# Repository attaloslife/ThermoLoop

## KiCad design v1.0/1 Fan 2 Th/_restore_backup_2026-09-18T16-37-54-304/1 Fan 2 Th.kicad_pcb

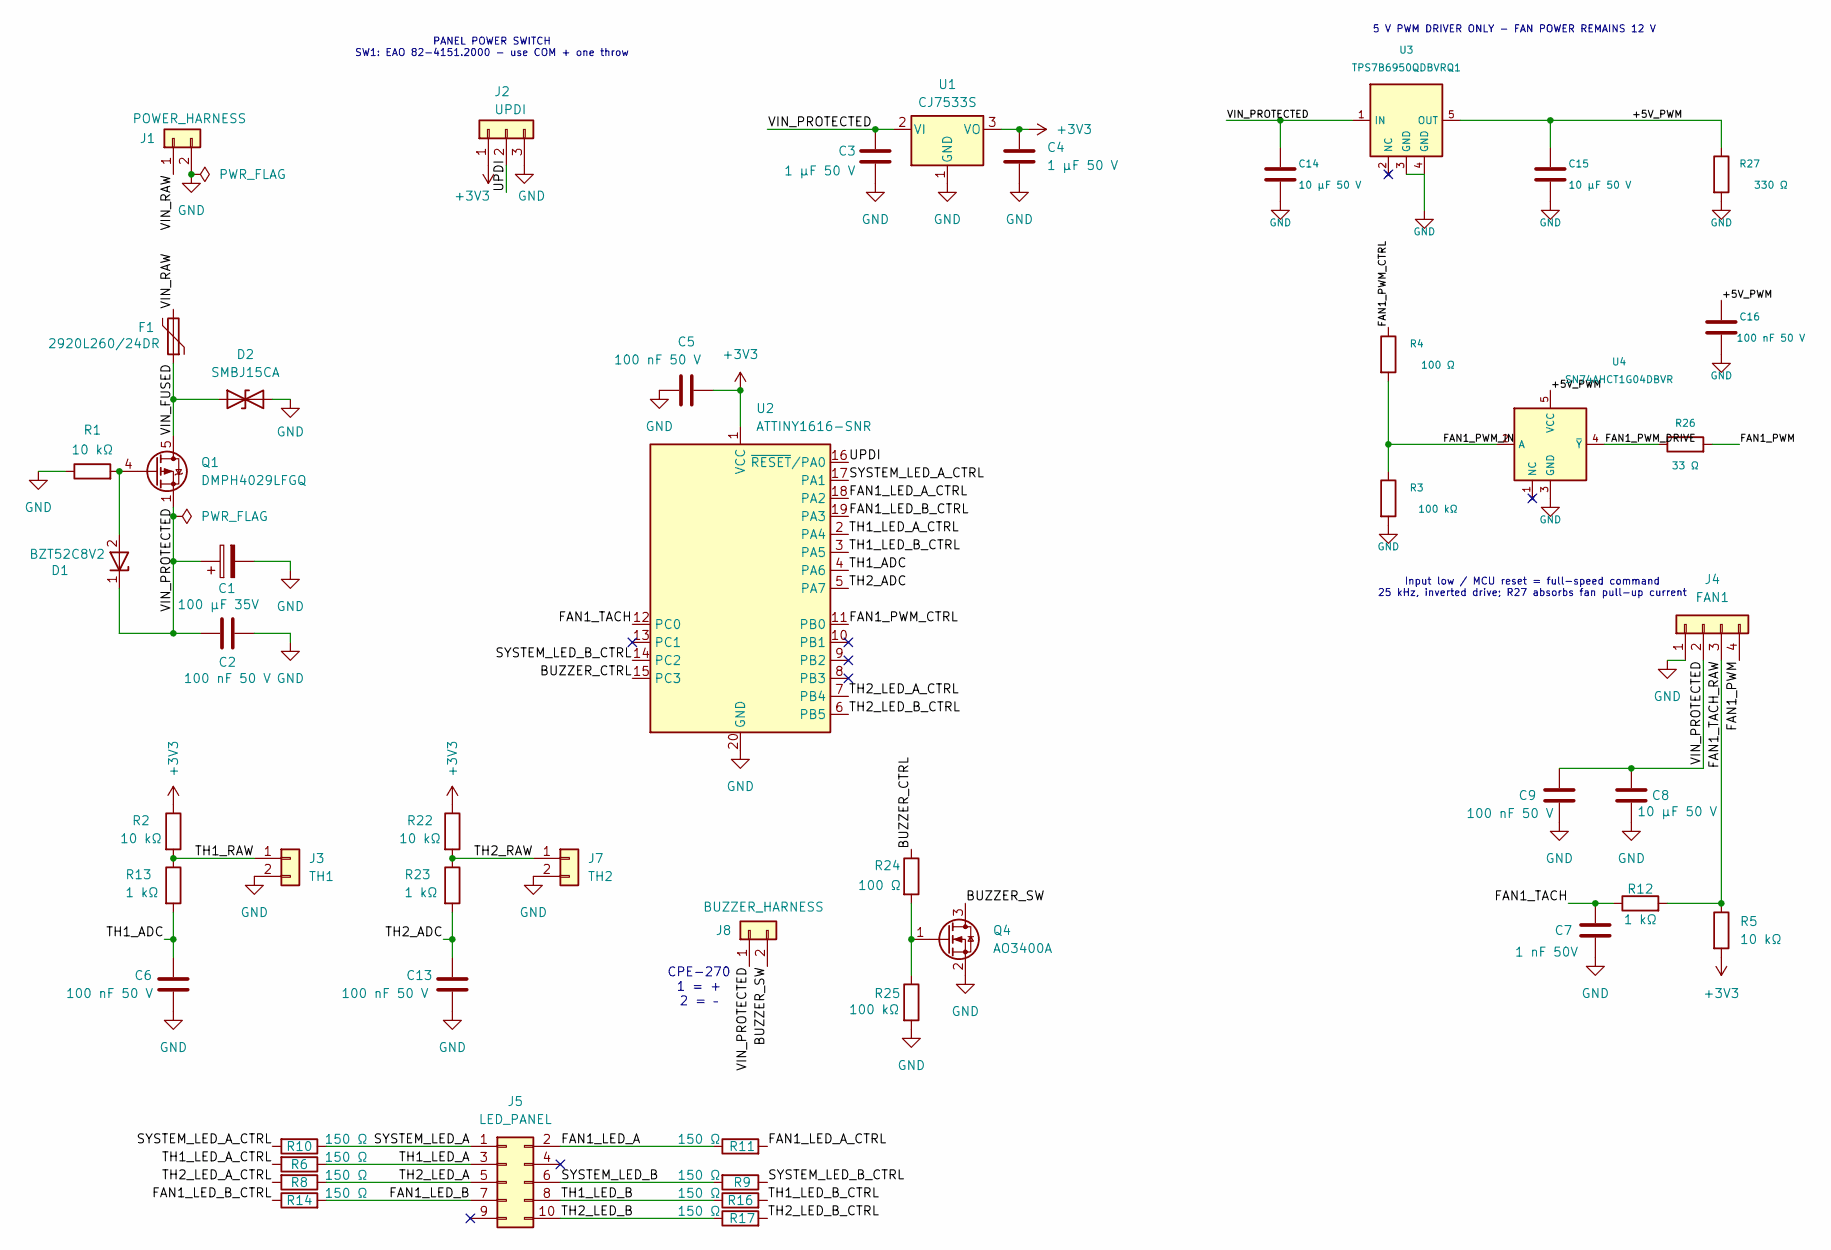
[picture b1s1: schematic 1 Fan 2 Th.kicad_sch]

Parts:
C1: 100 µF 35V; CP_Elec_6.3x7.7; MPN VZH101M1VTR-0607; JLCPCB C176683
C2, C5, C6, C9, C13, C16: 100 nF 50 V; C_0805_2012Metric; Tolerance ±10%; MPN CC0805KRX7R9BB104; JLCPCB C49678
C3, C4: 1 µF 50 V; C_0805_2012Metric; Tolerance ±10%; MPN CL21B105KBFNNNE; JLCPCB C28323
C7: 1 nF 50V; C_0805_2012Metric; Tolerance ±10%; MPN CL21B102KBCNNNC; JLCPCB C46653
C8, C14, C15: 10 µF 50 V; C_1210_3225Metric; MPN CL32B106KBJNNNE; JLCPCB C138687
D1: BZT52C8V2; D_SOD-123; MPN BZT52C8V2; JLCPCB C173432
D2: SMBJ15CA; D_SMB; MPN SMBJ15CA; JLCPCB C78809
F1: 2920L260/24DR; Fuse_2920_7451Metric; MPN 2920L260/24DR; JLCPCB C315904
J1: POWER_HARNESS; Molex_Micro-Fit_3.0_43045-0218_2x01-1MP_P3.00mm_Vertical; MPN 43045-0218; JLCPCB C476811
J2: UPDI; PinHeader_1x03_P2.54mm_Vertical; MPN 2.54-1*3PPin; JLCPCB C49257
J3: TH1; Molex_Micro-Fit_3.0_43045-0218_2x01-1MP_P3.00mm_Vertical; MPN 43045-0218; JLCPCB C476811
J4: FAN1; Molex_Micro-Fit_3.0_43045-0418_2x02-1MP_P3.00mm_Vertical; MPN 43045-0418; JLCPCB C293535
J5: LED_PANEL; Molex_Micro-Fit_3.0_43045-1018_2x05-1MP_P3.00mm_Vertical; MPN 43045-1018; JLCPCB C476814
J7: TH2; Molex_Micro-Fit_3.0_43045-0218_2x01-1MP_P3.00mm_Vertical; MPN 43045-0218; JLCPCB C476811
J8: BUZZER_HARNESS; Molex_Micro-Fit_3.0_43045-0218_2x01-1MP_P3.00mm_Vertical; MPN 43045-0218; JLCPCB C476811
Q1: DMPH4029LFGQ; Diodes_PowerDI3333-8; MPN DMPH4029LFGQ-7; JLCPCB C3279395
Q4: AO3400A; SOT-23; MPN AO3400A; JLCPCB C20917
R1, R2, R5, R22: 10 kΩ; R_0603_1608Metric; Tolerance ±1%; MPN 0603WAF1002T5E; JLCPCB C25804
R3, R25: 100 kΩ; R_0603_1608Metric; Tolerance ±1%; MPN 0603WAF1003T5E; JLCPCB C25803
R4, R24: 100 Ω; R_0603_1608Metric; Tolerance ±1%; MPN 0603WAF1000T5E; JLCPCB C22775
R6, R8, R9, R10, R11, R14, R16, R17: 150 Ω; R_0603_1608Metric; Tolerance ±1%; MPN 0603WAF1500T5E; JLCPCB C22808
R12, R13, R23: 1 kΩ; R_0603_1608Metric; Tolerance ±1%; MPN 0603WAF1001T5E; JLCPCB C21190
R26: 33 Ω; R_0603_1608Metric; Tolerance ±1%; MPN 0603WAF330JT5E; JLCPCB C23140
R27: 330 Ω; R_0805_2012Metric; Tolerance ±1%; MPN 0805W8F3300T5E; JLCPCB C17630
U1: CJ7533S; SOT-89-3; MPN CJ7533S; JLCPCB C2829417
U2: ATTINY1616-SNR; SOIC-20W_7.5x12.8mm_P1.27mm; MPN ATTINY1616-SNR; JLCPCB C609652
U3: TPS7B6950QDBVRQ1; SOT-23-5; MPN TPS7B6950QDBVRQ1; JLCPCB C132202
U4: SN74AHCT1G04DBVR; SOT-23-5; MPN SN74AHCT1G04DBVR; JLCPCB C30326

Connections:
+3V3: C4.1, C5.1, J2.1, R2.1, R5.2, R22.1, U1.3 (VO), U2.1 (VCC)
/+5V_PWM: C15.1, C16.1, R27.1, U3.5 (OUT), U4.5 (VCC)
/BUZZER_CTRL: R24.1, U2.15 (PC3)
/BUZZER_SW: J8.2, Q4.3 (D)
/FAN1_LED_A: J5.2, R11.1
/FAN1_LED_A_CTRL: R11.2, U2.18 (PA2)
/FAN1_LED_B: J5.7, R14.2
/FAN1_LED_B_CTRL: R14.1, U2.19 (PA3)
/FAN1_PWM: J4.4, R26.2
/FAN1_PWM_CTRL: R4.1, U2.11 (PB0)
/FAN1_PWM_DRIVE: R26.1, U4.4 (~Y)
/FAN1_PWM_IN: R3.1, R4.2, U4.2 (A)
/FAN1_TACH: C7.1, R12.1, U2.12 (PC0)
/FAN1_TACH_RAW: J4.3, R5.1, R12.2
/SYSTEM_LED_A: J5.1, R10.1
/SYSTEM_LED_A_CTRL: R10.2, U2.17 (PA1)
/SYSTEM_LED_B: J5.6, R9.2
/SYSTEM_LED_B_CTRL: R9.1, U2.14 (PC2)
/TH1_ADC: C6.1, R13.2, U2.4 (PA6)
/TH1_LED_A: J5.3, R6.1
/TH1_LED_A_CTRL: R6.2, U2.2 (PA4)
/TH1_LED_B: J5.8, R16.1
/TH1_LED_B_CTRL: R16.2, U2.3 (PA5)
/TH1_RAW: J3.1, R2.2, R13.1
/TH2_ADC: C13.1, R23.2, U2.5 (PA7)
/TH2_LED_A: J5.5, R8.1
/TH2_LED_A_CTRL: R8.2, U2.7 (PB4)
/TH2_LED_B: J5.10, R17.1
/TH2_LED_B_CTRL: R17.2, U2.6 (PB5)
/TH2_RAW: J7.1, R22.2, R23.1
/UPDI: J2.2, U2.16 (~RESET/PA0)
/VIN_FUSED: D2.1 (A1), F1.1, Q1.5 (D)
/VIN_PROTECTED: C1.1, C2.1, C3.1, C8.1, C9.1, C14.1, D1.1 (K), J4.2, J8.1, Q1.1 (S), Q1.2 (S), Q1.3 (S), U1.2 (VI), U3.1 (IN)
/VIN_RAW: F1.2, J1.1
GND: C1.2, C2.2, C3.2, C4.2, C5.2, C6.2, C7.2, C8.2, C9.2, C13.2, C14.2, C15.2, C16.2, D2.2 (A2), J1.2, J2.3, J3.2, J4.1, J7.2, Q4.2 (S), R1.1, R3.2, R25.2, R27.2, U1.1 (GND), U2.20 (GND), U3.3 (GND), U3.4 (GND), U4.3 (GND)
unnamed: D1.2 (A), Q1.4 (G), R1.2
unnamed: Q4.1 (G), R24.2, R25.1

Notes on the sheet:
PANEL POWER SWITCH SW1: EAO 82-4151.2000 - use COM + one throw
CPE-270 1 = + 2 = –
5 V PWM DRIVER ONLY - FAN POWER REMAINS 12 V
Input low / MCU reset = full-speed command 25 kHz, inverted drive; R27 absorbs fan pull-up current

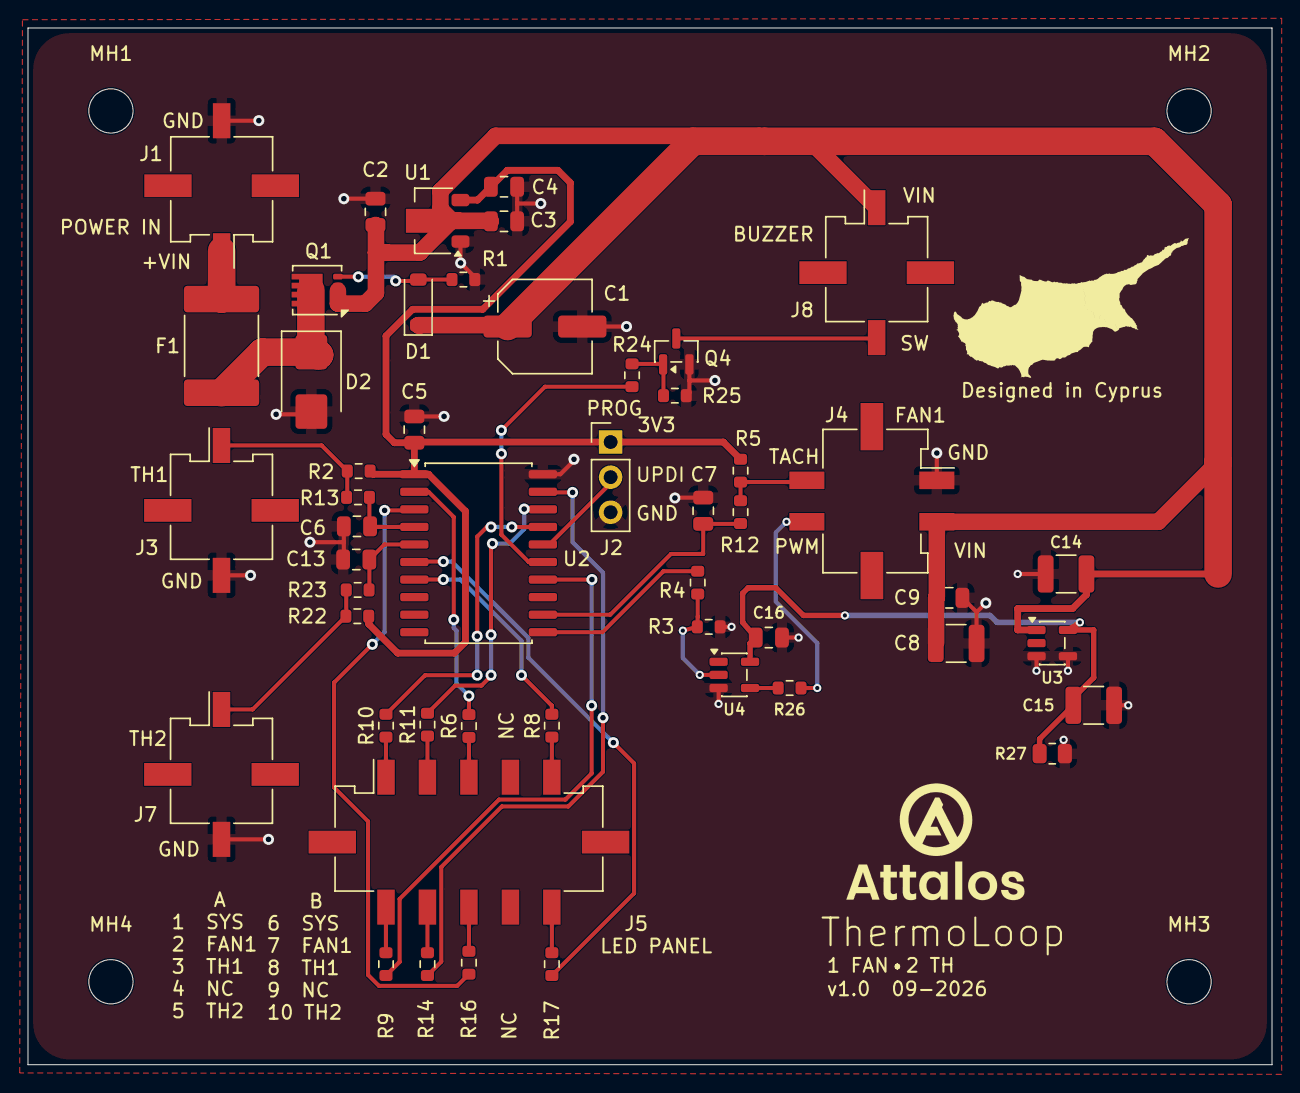
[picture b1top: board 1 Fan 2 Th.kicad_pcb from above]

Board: 2 copper layers, 90.0 x 75.0 mm, 54 parts (0 on the bottom side), 37 nets.

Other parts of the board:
MH1, MH2, MH3, MH4: MountingHole_3.2mm_M3

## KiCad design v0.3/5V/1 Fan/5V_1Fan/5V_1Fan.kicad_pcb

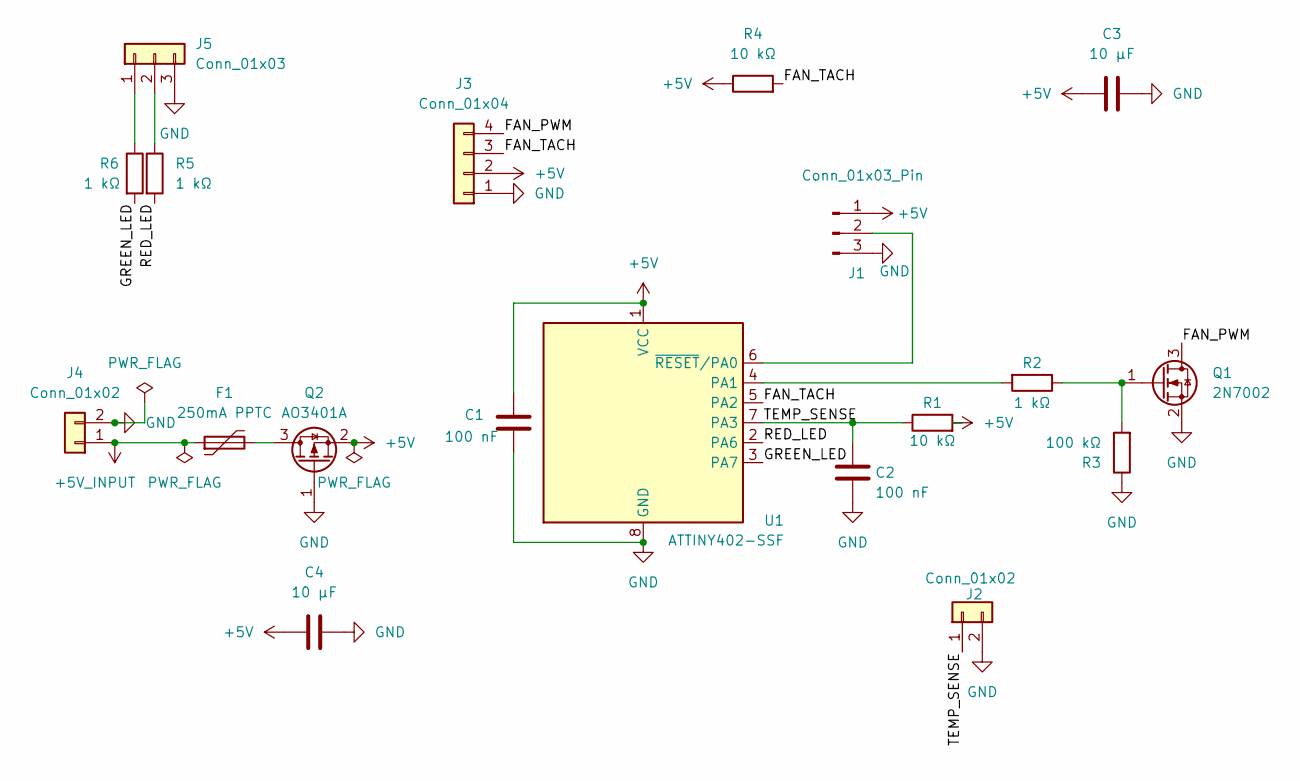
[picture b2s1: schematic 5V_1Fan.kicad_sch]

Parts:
C1, C2: 100 nF; C_0805_2012Metric_Pad1.18x1.45mm_HandSolder; MPN GRM21BR71H104KA01L; JLCPCB Part C77082
C3, C4: 10 µF; C_1206_3216Metric_Pad1.33x1.80mm_HandSolder; MPN TCC1206X7R106K160HT; JLCPCB Part C380363
F1: 250mA PPTC; Fuse_1206_3216Metric_Pad1.42x1.75mm_HandSolder; MPN 1206L025/24YR; JLCPCB Part C3762322
J1: Conn_01x03_Pin; PinHeader_1x03_P2.54mm_Vertical; MPN 2.54-1*3; JLCPCB Part C5116482
J2: Conn_01x02; JST_PH_B2B-PH-K_1x02_P2.00mm_Vertical; MPN B2B-PH-K-S; JLCPCB Part C20504437
J3: Conn_01x04; FanPinHeader_1x04_P2.54mm_Vertical; MPN 470531000; JLCPCB Part C240840
J4: Conn_01x02; JST_XH_B2B-XH-A_1x02_P2.50mm_Vertical; MPN B2B-XH-A(LF)(SN); JLCPCB Part C158012
J5: Conn_01x03; JST_PH_B3B-PH-K_1x03_P2.00mm_Vertical; MPN B3B-PH-K-S(LF)(SN); JLCPCB Part C131339
Q1: 2N7002; SOT-23; MPN 2N7002; JLCPCB Part C389059
Q2: AO3401A; SOT-23; MPN AO3401A; JLCPCB Part C15127
R1, R4: 10 kΩ; R_0805_2012Metric_Pad1.20x1.40mm_HandSolder; MPN RC0805FR-0710KL; JLCPCB Part C84376
R2, R5, R6: 1 kΩ; R_0805_2012Metric_Pad1.20x1.40mm_HandSolder; MPN RC0805FR-071KL; JLCPCB Part C95781
R3: 100 kΩ; R_0805_2012Metric_Pad1.20x1.40mm_HandSolder; MPN RC0805FR-07100KL; JLCPCB Part C96346
U1: ATTINY402-SSF; SOIC-8_3.9x4.9mm_P1.27mm; MPN ATTINY402-SSF; JLCPCB Part C1338236

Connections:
+5V: C1.1, C3.2, C4.1, J1.1, J3.2, Q2.2 (S), R1.2, R4.1, U1.1 (VCC)
+5V_INPUT: F1.1, J4.1
/FAN_PWM: J3.4, Q1.3 (D)
/FAN_TACH: J3.3, R4.2, U1.5 (PA2)
/GREEN_LED: R6.2, U1.3 (PA7)
/RED_LED: R5.2, U1.2 (PA6)
/TEMP_SENSE: C2.1, J2.1, R1.1, U1.7 (PA3)
GND: C1.2, C2.2, C3.1, C4.2, J1.3, J2.2, J3.1, J4.2, J5.3, Q1.2 (S), Q2.1 (G), R3.1, U1.8 (GND)
unnamed: J1.2, U1.6 (~RESET/PA0)
unnamed: J5.1, R6.1
unnamed: J5.2, R5.1
unnamed: Q1.1 (G), R2.1, R3.2
unnamed: F1.2, Q2.3 (D)
unnamed: R2.2, U1.4 (PA1)

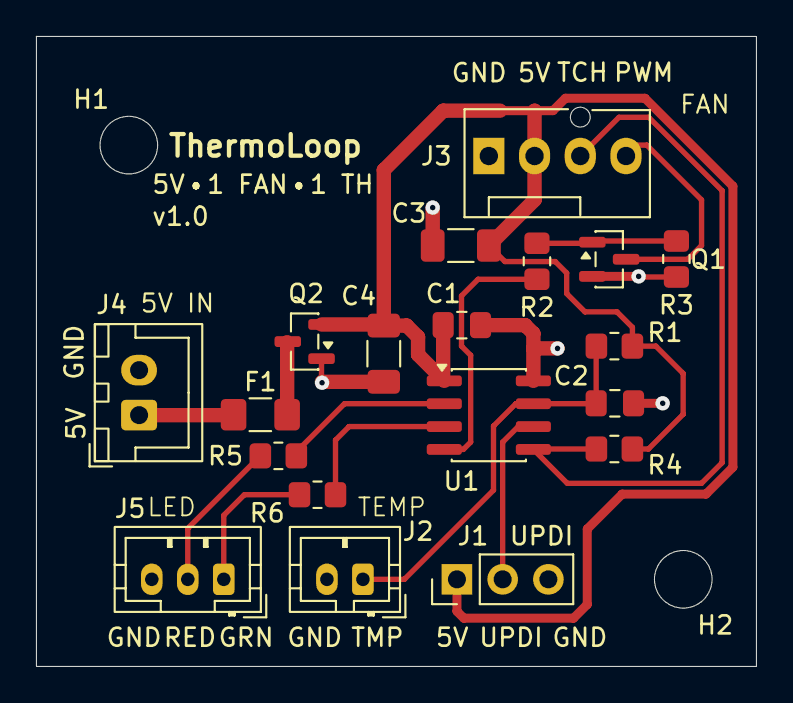
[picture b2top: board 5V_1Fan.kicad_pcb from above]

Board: 2 copper layers, 40.0 x 35.0 mm, 21 parts (0 on the bottom side), 14 nets.

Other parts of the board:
H1, H2: MountingHole_3.2mm_M3_DIN965

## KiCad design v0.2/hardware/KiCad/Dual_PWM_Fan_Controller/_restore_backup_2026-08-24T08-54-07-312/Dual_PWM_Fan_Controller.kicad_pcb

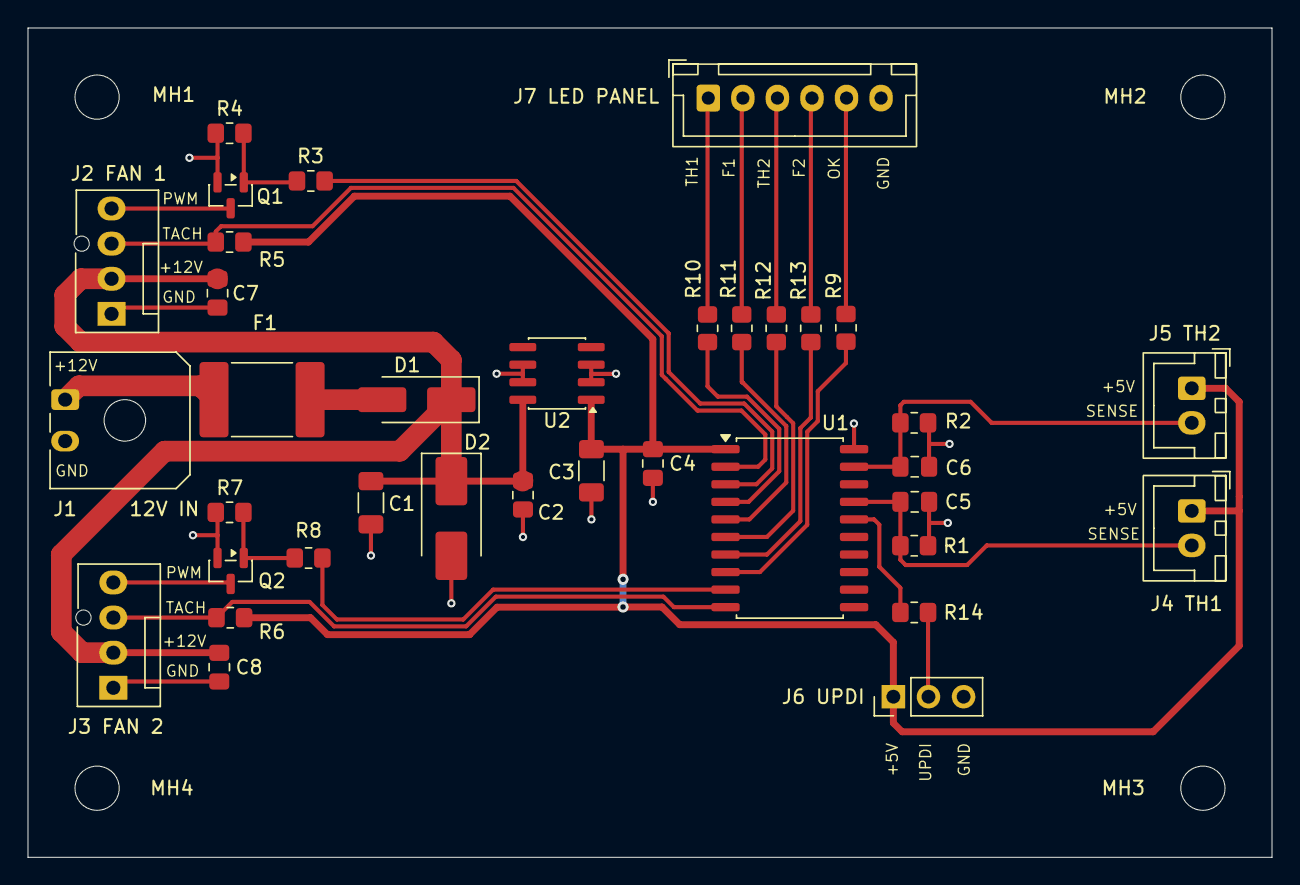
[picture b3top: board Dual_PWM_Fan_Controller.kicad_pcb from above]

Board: 2 copper layers, 90.0 x 60.0 mm, 40 parts (0 on the bottom side), 27 nets.

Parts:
C1: 10uF 25V; C_1206_3216Metric_Pad1.33x1.80mm_HandSolder
C2, C4, C5, C6, C7, C8: 100nF; C_0805_2012Metric_Pad1.18x1.45mm_HandSolder
C3: 10uF 16V; C_1206_3216Metric_Pad1.33x1.80mm_HandSolder
D1: SS34; D_SMA_Handsoldering
D2: SMBJ15A; D_SMB_Handsoldering
F1: 3A; Fuse_2920_7451Metric_Pad2.10x5.45mm_HandSolder
J1     12V IN: Conn_01x02; Molex_Micro-Fit_3.0_43650-0200_1x02_P3.00mm_Horizontal
J2 FAN 1, J3 FAN 2: Conn_01x04; FanPinHeader_1x04_P2.54mm_Vertical
J4 TH1, J5 TH2: Conn_01x02; JST_XH_B2B-XH-A_1x02_P2.50mm_Vertical
J6 UPDI: Conn_01x03; PinHeader_1x03_P2.54mm_Vertical
J7 LED PANEL: LED Panel; JST_XH_B6B-XH-A_1x06_P2.50mm_Vertical
MH1, MH2, MH3, MH4: MountingHole_3.2mm_M3
Q1, Q2: 2N7002; SOT-23
R1, R2: 10k 1%; R_0805_2012Metric_Pad1.20x1.40mm_HandSolder
R3, R8: 100Ω; R_0805_2012Metric_Pad1.20x1.40mm_HandSolder
R4, R7: 100kΩ; R_0805_2012Metric_Pad1.20x1.40mm_HandSolder
R5, R6: 10kΩ; R_0805_2012Metric_Pad1.20x1.40mm_HandSolder
R9, R10, R11, R12, R13: 1kΩ; R_0805_2012Metric_Pad1.20x1.40mm_HandSolder
R14: 470Ω; R_0805_2012Metric_Pad1.20x1.40mm_HandSolder
U1: ATtiny1616-S; SOIC-20W_7.5x12.8mm_P1.27mm
U2: L78L05_SO8; SOIC-8_3.9x4.9mm_P1.27mm

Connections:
+5V: C3.1, C4.2, J4 TH1.1, J5 TH2.1, J6 UPDI.1, R5.1, R6.2, U1.1 (VCC), U2.1 (OUT)
/+12V_FUSED: D1.2 (A), F1.2
/+12V_IN: F1.1, J1 12V IN.1
/+12V_PROTECTED: C1.2, C2.1, C7.2, C8.1, D1.1 (K), D2.1 (A1), J2 FAN 1.2, J3 FAN 2.2, U2.8 (IN)
/FAN1_PWM: J2 FAN 1.4, Q1.3 (D)
/FAN1_TACH: J2 FAN 1.3, R5.2, U1.2 (PA4)
/FAN2_PWM: J3 FAN 2.4, Q2.3 (D)
/FAN2_TACH: J3 FAN 2.3, R6.1, U1.10 (PB1)
/LED_FAN1_FAULT: J7 LED PANEL.2, R11.2
/LED_FAN2_FAULT: J7 LED PANEL.4, R13.2
/LED_OK: J7 LED PANEL.5, R9.2
/LED_TH1_FAULT: J7 LED PANEL.1, R10.1
/TH1_SENSE: C5.1, J4 TH1.2, R1.1, U1.17 (PA1)
/TH2_FAULT: J7 LED PANEL.3, R12.2
/TH2_SENSE: C6.1, J5 TH2.2, R2.1, U1.19 (PA3)
/UPDI: R14.2, U1.16 (~RESET/PA0)
GND: C1.1, C2.2, C3.2, C4.1, C5.2, C6.2, C7.1, C8.2, D2.2 (A2), J1 12V IN.2, J2 FAN 1.1, J3 FAN 2.1, J6 UPDI.3, J7 LED PANEL.6, Q1.2 (S), Q2.2 (S), R1.2, R2.2, R4.2, R7.2, U1.20 (GND), U2.2 (GND), U2.3 (GND), U2.6 (GND), U2.7 (GND)
unnamed: J6 UPDI.2, R14.1
unnamed: Q1.1 (G), R3.1, R4.1
unnamed: Q2.1 (G), R7.1, R8.2
unnamed: R3.2, U1.3 (PA5)
unnamed: R10.2, U1.4 (PA6)
unnamed: R11.1, U1.5 (PA7)
unnamed: R8.1, U1.9 (PB2)
unnamed: R9.1, U1.8 (PB3)
unnamed: R13.1, U1.7 (PB4)
unnamed: R12.1, U1.6 (PB5)
